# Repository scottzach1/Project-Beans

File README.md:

# Group 3 - Project beans

## Welcome to Project Beans.

Project Beans was a 2020 project by 6 VUW Engineering students to
deliver a model rocket for a client. An in-depth breakdown of the
projects scope, deliverables and current state can be obtained in-depth
within the documentation of this repository.

> Figure 1: Rocket Design Render

## Meet The Team

### Software

|  |  |  |
|:------------------------------------------------------------------------------------------------------------------------------------------------------|:---------------------------------------------------------------------------------------------------------------|:--------------------------------------------------------------------------------------------------------------|
| [Zac Scott](https://github.com/scottzach1)                                                                                                            | [Ron Crisostomo](https://github.com/crisosron)                                                                 | [Finlay Sargisson](https://github.com/sarrgi)                                                                 |

### Hardware

|  |  |  |
|:-------------------------------------------------------------------------------------------------------------------------------------------------------------|:-----------------------------------------------------------------------------------------------------------------|:---------------------------------------------------------------------------------------------------------------------------------------------|
| [Niels Clayton](https://github.com/Niels-Clayton)                                                                                                            | [William Fowler](https://github.com/Will-Fowler)                                                                 | [Billy Rob](https://gitlab.ecs.vuw.ac.nz/robbbill)                                                                                           |

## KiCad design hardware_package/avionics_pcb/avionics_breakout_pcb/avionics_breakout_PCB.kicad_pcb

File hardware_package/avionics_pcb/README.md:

# Avionics PCB's

> Description of the different avionics PCB's and libraries

## KiCad

- All PCB's will be designed using the KiCad Cross Platform and Open Source Electronics Design Automation Suite. A selection of custom footprints and symbols used in the following projects can be found in the `kicad_lib/` directory.

- All PCB's within this directory will be subject to standard ERC and DRC rule checks, which will be performed and checked by the CI pipeline.

## PCB's

| File             | Description       |
|:-----------------|:------------------|
| `avionics_base_station/`  | The avionics base station PCB will be used to connect the RFM98 LoRa radio to the [ESP8266 microcontroller](https://www.espressif.com/en/products/socs/esp8266), maintaining a small form-factor. This board is designed to be the final base station product. |
| `avionics_breakout_PCB/`  | The avionics breakout PCB will is the second prototype of the rocket hardware. This PCB will take all of the testing breakout boards that can be found [here](../bill_of_materials/bill_of_materials.md) in the BOM, and will integrate all of then onto a single compact board that is limited to a single side. This board will be used for extensive testing of the hardware in unison. |
| `Final_PCB/` | The avionics final PCB is the final iteration of the PCB. This board will take all of the individual components found on each of the breakouts, and will place them onto a single PCB. This board will also include power supplies for all components, including the ignition circuitry and servo motors.  |

## Libraries

| File             | Description       |
|:-----------------|:------------------|
| `kicad_lib/` | This directory contains a selection of custom footprints and symbols that have been used in the PCB's. This library currently contains footprints for the following parts:

- Adafruit Feather STM32F4D5 Breakout
- ESP8266 Node MCU microcontroller breakout
- Adafruit MPL3115A2 Barometer Breakout
- Adafruit MPU 6050 Breakout
- RFM98 LoRa Radio

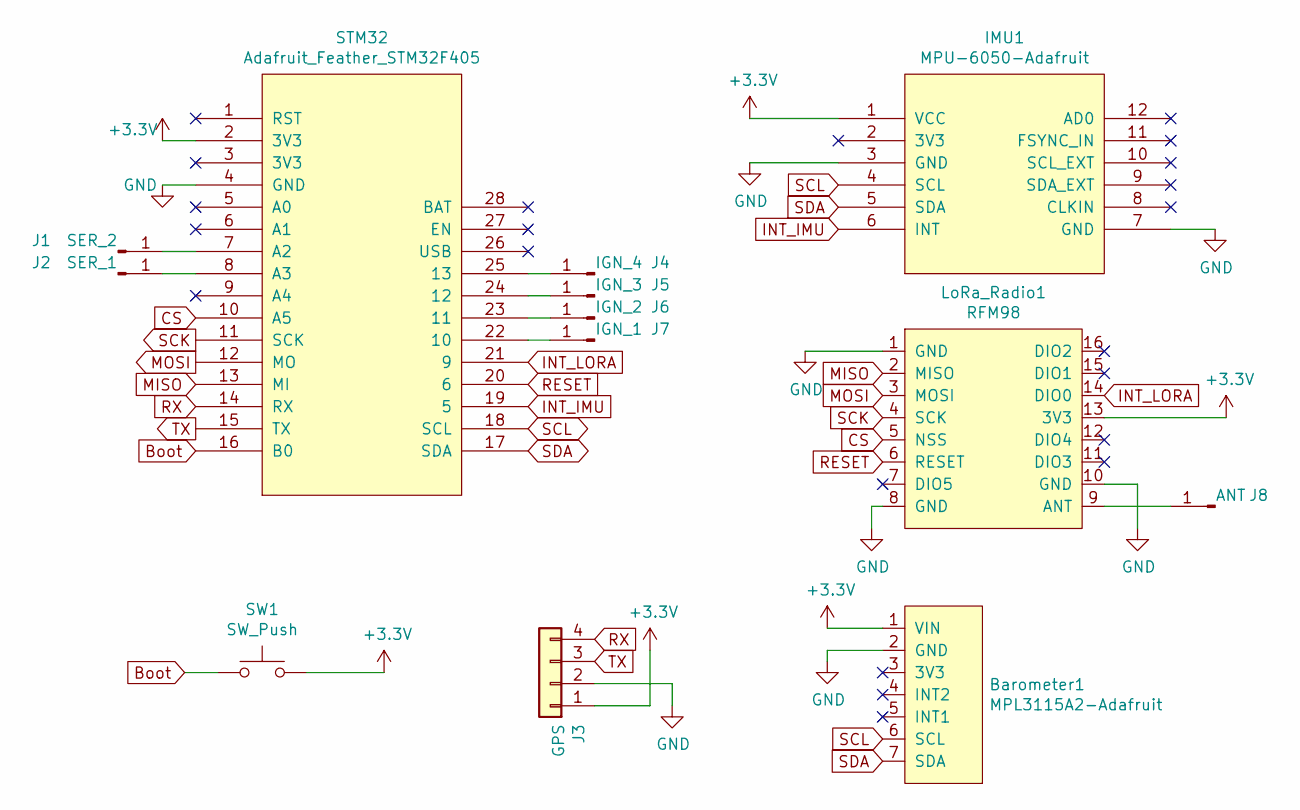
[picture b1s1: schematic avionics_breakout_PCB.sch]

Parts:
Barometer1: MPL3115A2-Adafruit
IMU1: MPU-6050-Adafruit; MPU6050-adafruit
J1: SER_2; SolderWire-0.1sqmm_1x01_D0.4mm_OD1mm
J2: SER_1; SolderWire-0.1sqmm_1x01_D0.4mm_OD1mm
J3: GPS; PinHeader_1x04_P2.54mm_Vertical
J4: IGN_4; SolderWire-0.1sqmm_1x01_D0.4mm_OD1mm
J5: IGN_3; SolderWire-0.1sqmm_1x01_D0.4mm_OD1mm
J6: IGN_2; SolderWire-0.1sqmm_1x01_D0.4mm_OD1mm
J7: IGN_1; SolderWire-0.1sqmm_1x01_D0.4mm_OD1mm
J8: ANT; SolderWire-0.1sqmm_1x01_D0.4mm_OD1mm
LoRa_Radio1: RFM98
STM32: Adafruit_Feather_STM32F405
SW1: SW_Push; SW_PUSH_6mm

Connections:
+3V3: Barometer1.1 (VIN), IMU1.1 (VCC), J3.1, LoRa_Radio1.13 (3V3), STM32.2 (3V3), SW1.2
Boot: STM32.16 (B0), SW1.1
CS: LoRa_Radio1.5 (NSS), STM32.10 (A5)
GND: Barometer1.2 (GND), IMU1.3 (GND), IMU1.7 (GND), J3.2, LoRa_Radio1.1 (GND), LoRa_Radio1.8 (GND), LoRa_Radio1.10 (GND), STM32.4 (GND)
INT_IMU: IMU1.6 (INT), STM32.19 (5)
INT_LORA: LoRa_Radio1.14 (DIO0), STM32.21 (9)
MISO: LoRa_Radio1.2 (MISO), STM32.13 (MI)
MOSI: LoRa_Radio1.3 (MOSI), STM32.12 (MO)
unnamed: J1.1, STM32.7 (A2)
unnamed: J2.1, STM32.8 (A3)
unnamed: J4.1, STM32.25 (13)
unnamed: J5.1, STM32.24 (12)
unnamed: J6.1, STM32.23 (11)
unnamed: J7.1, STM32.22 (10)
unnamed: J8.1, LoRa_Radio1.9 (ANT)
RESET: LoRa_Radio1.6 (RESET), STM32.20 (6)
RX: J3.4, STM32.14 (RX)
SCK: LoRa_Radio1.4 (SCK), STM32.11 (SCK)
SCL: Barometer1.6 (SCL), IMU1.4 (SCL), STM32.18 (SCL)
SDA: Barometer1.7 (SDA), IMU1.5 (SDA), STM32.17 (SDA)
TX: J3.3, STM32.15 (TX)

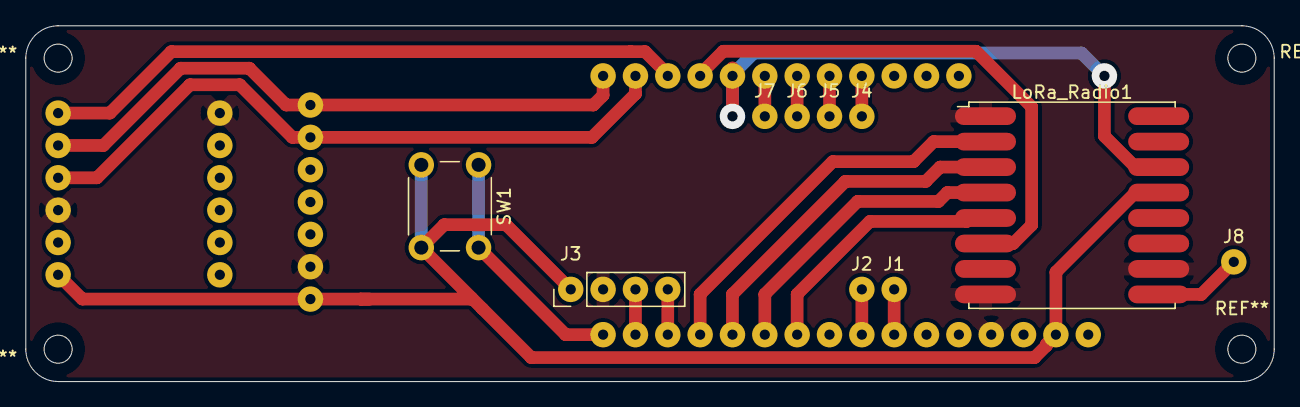
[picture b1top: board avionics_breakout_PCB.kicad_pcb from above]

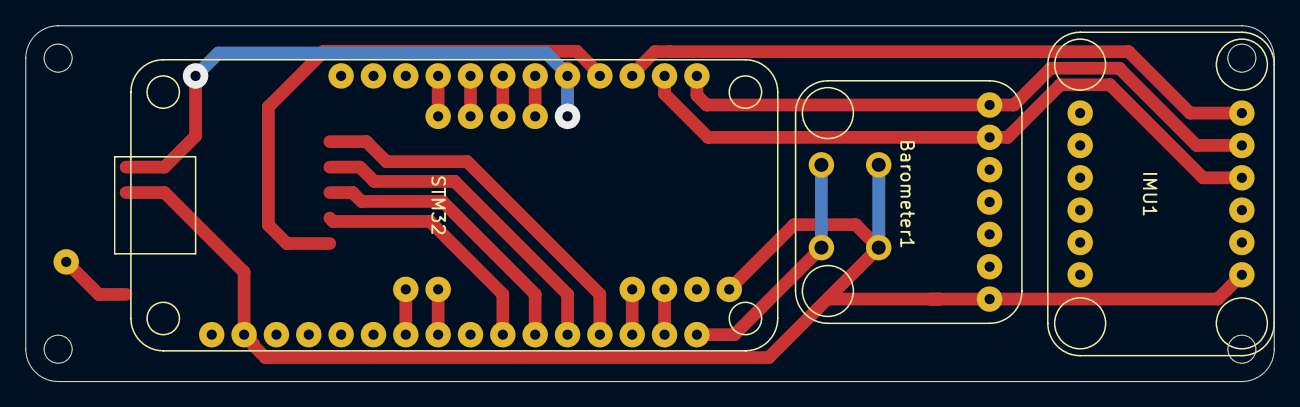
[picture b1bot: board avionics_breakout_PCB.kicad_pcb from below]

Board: 2 copper layers, 98.0 x 27.9 mm, 13 parts (3 on the bottom side), 21 nets.

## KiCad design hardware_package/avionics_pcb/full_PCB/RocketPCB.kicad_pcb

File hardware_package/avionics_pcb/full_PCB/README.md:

## Full PCB - Prototype 1 - Documentation

This PCB is designed to accomodate the STM32F405 processor, the accompanying sensors and peripherals, power circuitry and supporting passive and active electronic components required by the avionics package.

### Schematic
For the schematic we wanted to integrate as many components into the avionics package board as possible to reduce the size and cost associated with manufacutring. In this case the only sensors that are not integrated into the board are the MPU-6050, the GPS and the LoRa radio tranceiver which are on breakout boards connected by headers.

#### Power circuitry
The avionics package is designed to be powered off of a 2-cell LiPo battery supplying a nominal voltage of 7.4V. This is connected to the avionics board via a 3 pin JST connector. Included in series with the +7.4V pin is a fet and polyfuse to protect against reverse polarity and over current. The 7.4V is then passed to two regulator, a 3.3V linear regulator capable of supply up to 1A for the microprocessor and periphals and a 6V switching regulator capable of supplying up to 2A to both of the servos. So there is a +3.3V and a +6V rail. The ground is referenced to the negative terminal of the battery.

Regarding the 3.3V regulator, a fet and diode are included at the input so that when the battery is connected the 5V supplied by the voltage bus of the USB-C port is cut off by the fet. If the battery is not connected then the device can be powered off of the USB-C port. For verification and debug purporses, LEDs and test points were included at the output of both regulators and an additional test point included for ground. Lastly decoupling capacitors were included between the power rails and power inputs of each of the ICs to isolate any potential noise sources from interfering with the rest of the system.

#### STM32F405 and Adafruit feather design
The STM32F405 was chosen as our design is based on the Adafruit STM32F405 Feather Express development board [available here](https://learn.adafruit.com/adafruit-stm32f405-feather-express/downloads). From this development board we kept the microSD port, the USB-C connector, flash memory, and a redesigned 3.3V regulator. Components and features that we did not integrated from the Adafruit Feather included the USB battery charger and NeoPixel programmable LED. The battery charger was not included as this functionality would make the avionics package bulkier and it is not practical to charge a 2-cell LiPo using USB.

Both of the external oscillator crystals included in the Adafruit feather were not included in the design as the STM32F405 already contains a high speed internal RC oscillator which runs at 16MHz.

#### Sensors and peripherals
For the sensors and periphals, included in the schematic are the IMU, Lora radio tranceiver, barometer and GPS. All of these aside from the barometer are integrated into the PCB. The IMU, radio and gps have pads to connect the breakoutboards for these components via headers. The GPS, barometer and IMU all communicate via I2C protocol while the flash memory and radio module communicate via SPI protocol.

All the sensors and breakout boards are based off of Adafruit designs listed below:
[GPS](https://learn.adafruit.com/adafruit-mini-gps-pa1010d-module)
[Radio Tranceiver](https://learn.adafruit.com/adafruit-rfm69hcw-and-rfm96-rfm95-rfm98-lora-packet-padio-breakouts/downloads)
[IMU](https://learn.adafruit.com/mpu6050-6-dof-accelerometer-and-gyro?view=all)
[Barometer](https://learn.adafruit.com/using-mpl3115a2-with-circuitpython)

### PCB design
The PCB design uses 4 layers, the top and bottom are for signals, the 2nd layer is a ground plane and the 3rd layer is a +3.3V plane. The PCB can be sectioned into the power supply, breakout board pads, microprocessor, microSD card port, flash memory and barometer, all including their respective supporting components. Most of the anlogue circuity was segrated from the digital components to minimize EMI.

In terms of footprints, aside form the breakoutboard pads, pads for the futaba JR connectors, the poly fuse and flash memory, all the other footprints are surface mounted. This is to ensure the package remains small and compact.

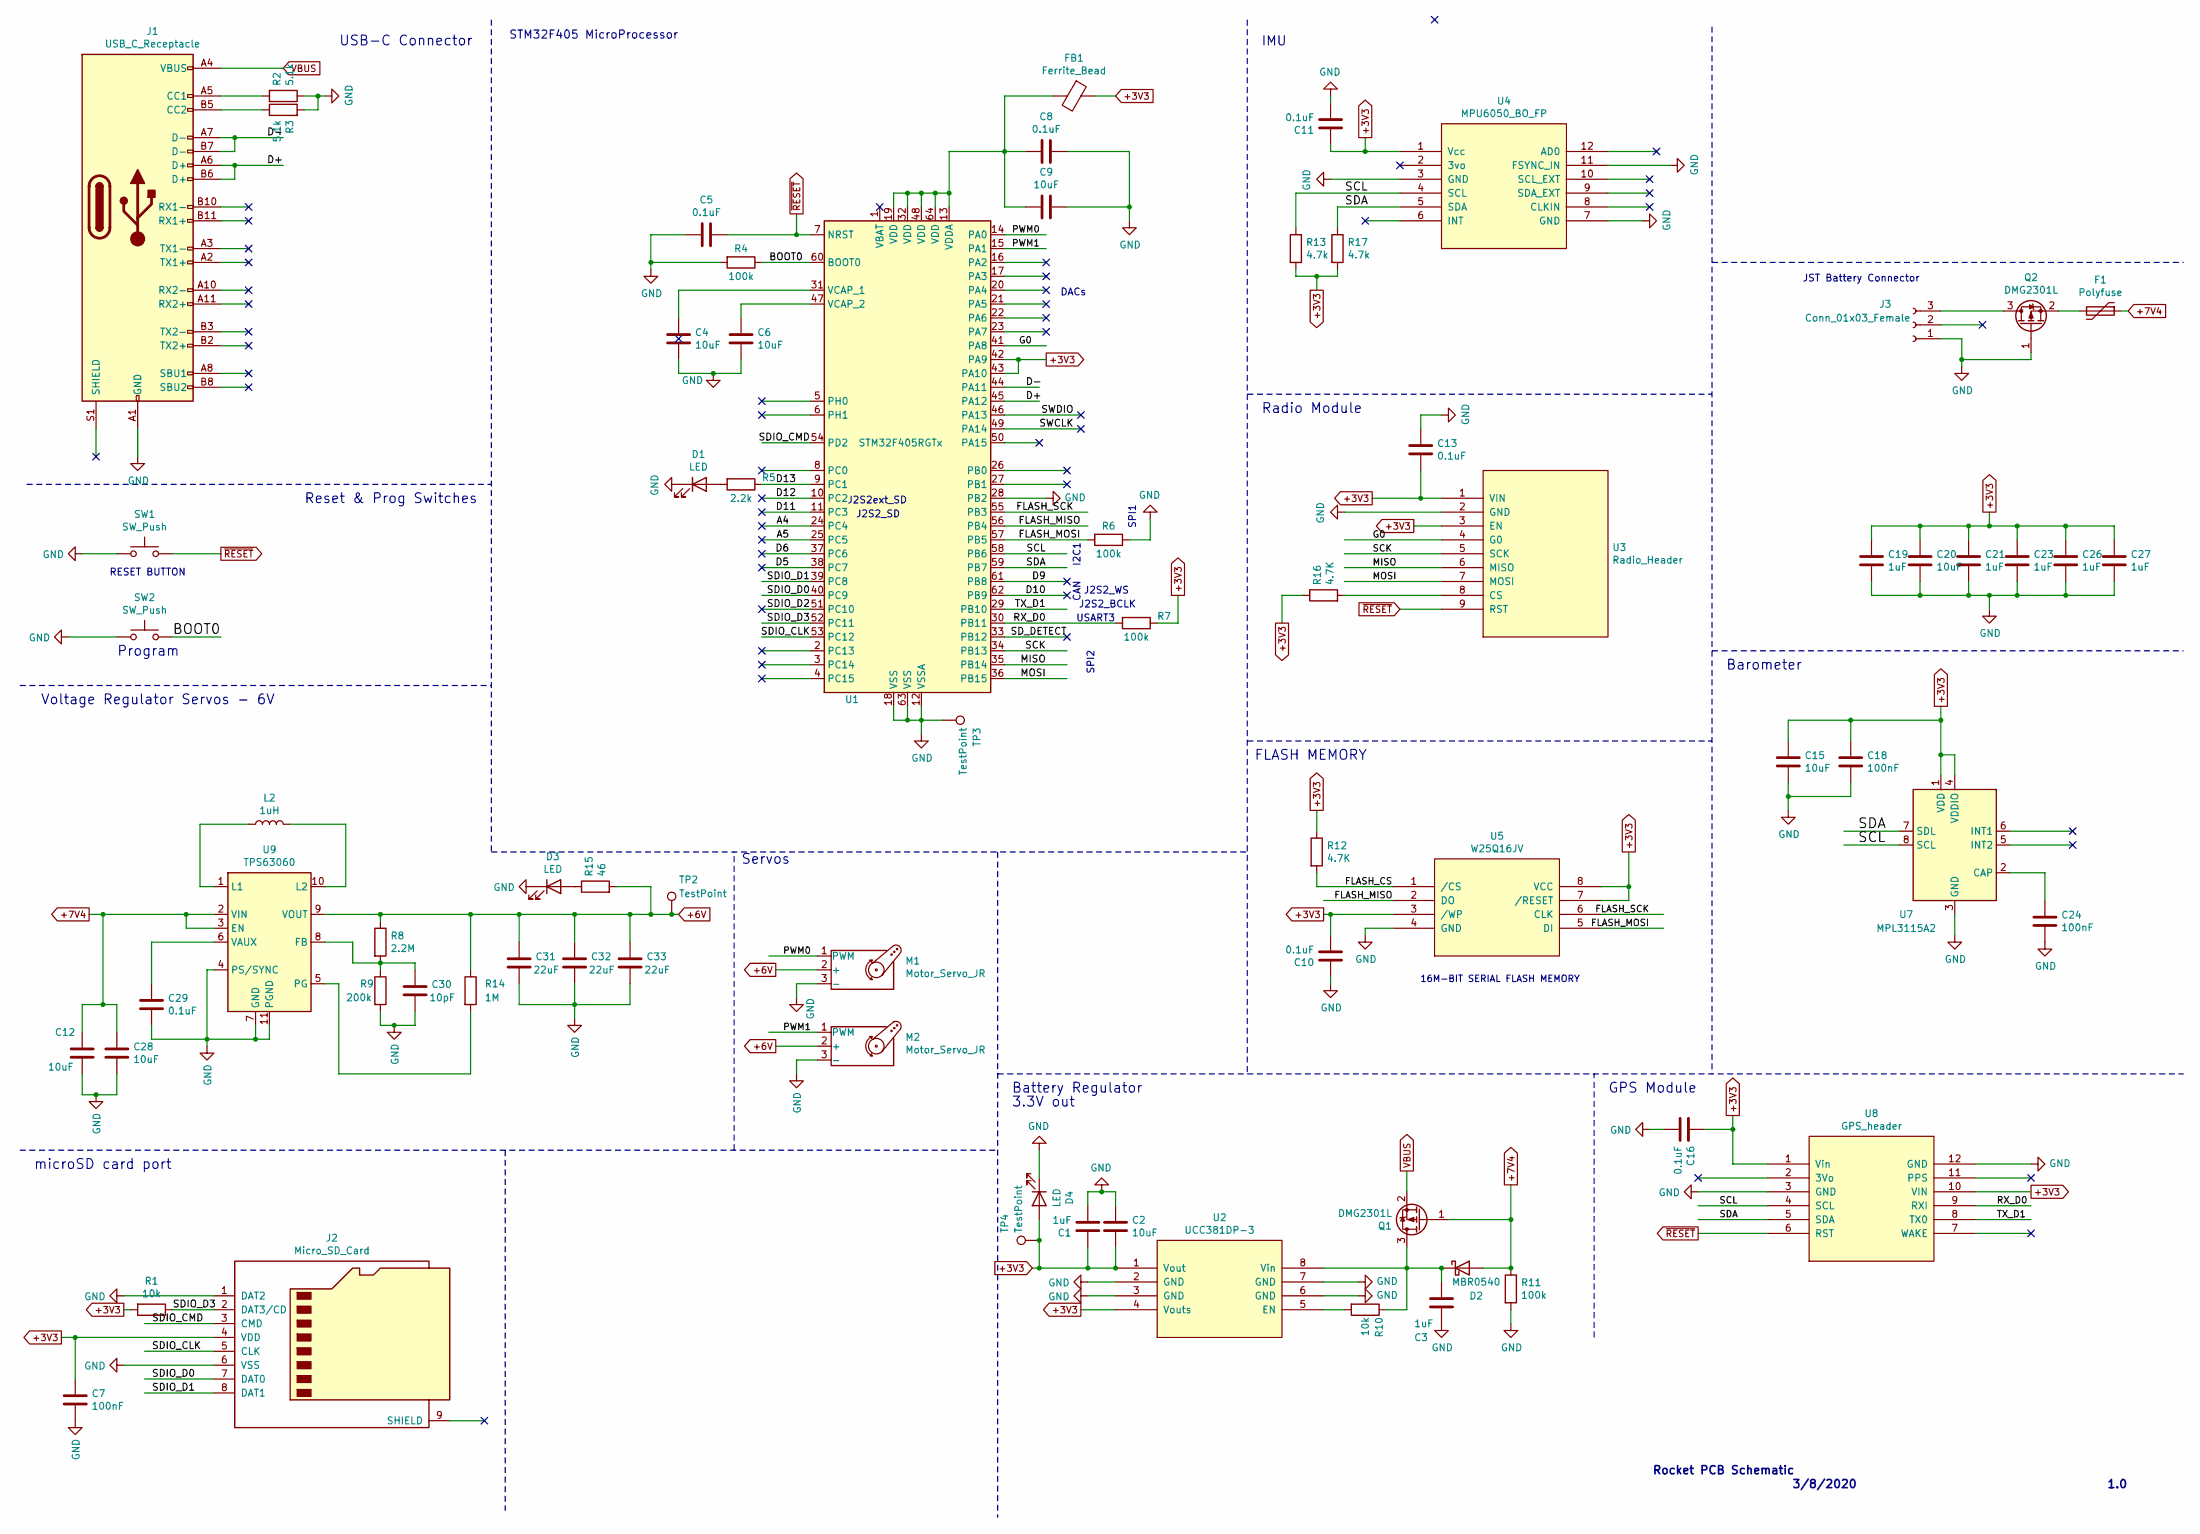
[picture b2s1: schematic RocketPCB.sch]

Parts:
C1, C3, C19, C21, C23, C26, C27: 1uF; C_0603_1608Metric
C2, C4, C6, C9, C12, C15, C20, C28: 10uF; C_0805_2012Metric
C5, C8, C10, C11, C13, C16, C29: 0.1uF; C_0603_1608Metric
C7, C18, C24: 100nF; C_0603_1608Metric
C30: 10pF; C_0603_1608Metric
C31, C32, C33: 22uF; C_0805_2012Metric
D1, D3, D4: LED; LED_0603_1608Metric_Pad1.05x0.95mm_HandSolder
D2: MBR0540; D_SOD-123
F1: Polyfuse; Fuse_Littelfuse_395Series
FB1: Ferrite_Bead; R_0402_1005Metric
J1: USB_C_Receptacle; USB_C_Receptacle_Palconn_UTC16-G
J2: Micro_SD_Card; microSD_HC_Hirose_DM3BT-DSF-PEJS
J3: Conn_01x03_Female; JST_XH_B3B-XH-A_1x03_P2.50mm_Vertical
L2: 1uH; L_0805_2012Metric
M1, M2: Motor_Servo_JR; JR_servo_connector
Q1, Q2: DMG2301L; SOT-23
R1, R10: 10k; R_0603_1608Metric
R2, R3: 5.1k; R_0603_1608Metric
R4, R6, R7, R11: 100k; R_0603_1608Metric
R5: 2.2k; R_0603_1608Metric
R8: 2.2M; R_0603_1608Metric
R9: 200k; R_0603_1608Metric
R12, R16: 4.7K; R_0603_1608Metric
R13, R17: 4.7k; R_0603_1608Metric
R14: 1M; R_0603_1608Metric
R15: 46; R_0603_1608Metric
SW1, SW2: SW_Push; SW_Push_SPST_NO_Alps_SKRK
TP2, TP3, TP4: TestPoint; TestPoint_Pad_D1.0mm
U1: STM32F405RGTx; LQFP-64_10x10mm_P0.5mm
U2: UCC381DP-3; SOIC127P599X175-8N
U3: Radio_Header; gps_header_footprint
U4: MPU6050_BO_FP; MPU6050-footprint
U5: W25Q16JV; W25Q16JV_footprint
U7: MPL3115A2; NXP_LGA-8_3x5mm_P1.25mm_H1.1mm
U8: GPS_header; GPS_header_fp
U9: TPS63060; Texas_S-PWSON-N10_ThermalVias

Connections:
+3V3: C1.1, C2.2, C7.1, C10.2, C11.1, C13.2, C15.1, C16.1, C18.1, C19.1, C20.1, C21.1, C23.1, C26.1, C27.1, D4.2 (A), FB1.1, J2.4 (VDD), R1.2, R7.1, R12.1, R13.2, R16.1, R17.2, TP4.1, U1.42 (PA9), U1.43 (PA10), U2.1 (Vout), U2.4 (Vouts), U3.1 (VIN), U3.3 (EN), U4.1 (Vcc), U5.3 (/WP), U5.7 (/RESET), U5.8 (VCC), U7.1 (VDD), U7.4 (VDDIO), U8.1 (Vin), U8.10 (VIN)
+6V: C31.1, C32.1, C33.1, M1.2 (+), M2.2 (+), R8.1, R14.1, R15.2, TP2.1, U9.9 (VOUT)
+7V4: C12.1, C28.1, D2.2 (A), F1.1, Q1.1 (G), R11.1, U9.2 (VIN), U9.3 (EN)
/A4: U1.24 (PC4)
/A5: U1.25 (PC5)
/BOOT0: R4.1, SW2.2, U1.60 (BOOT0)
/D5: U1.38 (PC7)
/D6: U1.37 (PC6)
/D9: U1.61 (PB8)
/D10: U1.62 (PB9)
/D11: U1.11 (PC3)
/D12: U1.10 (PC2)
/D13: R5.1, U1.9 (PC1)
/D+: J1.A6 (D+), J1.B6 (D+), U1.45 (PA12)
/D-: J1.A7 (D-), J1.B7 (D-), U1.44 (PA11)
/FLASH_CS: R12.2, U5.1 (/CS)
/FLASH_MISO: U1.56 (PB4), U5.2 (DO)
/FLASH_MOSI: R6.2, U1.57 (PB5), U5.5 (DI)
/FLASH_SCK: U1.55 (PB3), U5.6 (CLK)
/G0: U1.41 (PA8), U3.4 (G0)
/MISO: U1.35 (PB14), U3.6 (MISO)
/MOSI: U1.36 (PB15), U3.7 (MOSI)
/PWM0: M1.1 (PWM), U1.14 (PA0)
/PWM1: M2.1 (PWM), U1.15 (PA1)
/RX_D0: R7.2, U1.30 (PB11), U8.9 (RXI)
/SCK: U1.34 (PB13), U3.5 (SCK)
/SCL: R13.1, U1.58 (PB6), U4.4 (SCL), U7.8 (SCL), U8.4 (SCL)
/SDA: R17.1, U1.59 (PB7), U4.5 (SDA), U7.7 (SDL), U8.5 (SDA)
/SDIO_CLK: J2.5 (CLK), U1.53 (PC12)
/SDIO_CMD: J2.3 (CMD), U1.54 (PD2)
/SDIO_D0: J2.7 (DAT0), U1.40 (PC9)
/SDIO_D1: J2.8 (DAT1), U1.39 (PC8)
/SDIO_D2: U1.51 (PC10)
/SDIO_D3: J2.2 (DAT3/CD), R1.1, U1.52 (PC11)
/SD_DETECT: U1.33 (PB12)
/SWCLK: U1.49 (PA14)
/SWDIO: U1.46 (PA13)
/TX_D1: U1.29 (PB10), U8.8 (TX0)
GND: C1.2, C2.1, C3.2, C4.2, C5.1, C6.2, C7.2, C8.2, C9.2, C10.1, C11.2, C12.2, C13.1, C15.2, C16.2, C18.2, C19.2, C20.2, C21.2, C23.2, C24.2, C26.2, C27.2, C28.2, C29.2, C30.2, C31.2, C32.2, C33.2, D1.1 (K), D3.1 (K), D4.1 (K), J1.A1 (GND), J1.A12 (GND), J1.B1 (GND), J1.B12 (GND), J2.1 (DAT2), J2.6 (VSS), J3.1, M1.3 (-), M2.3 (-), Q2.1 (G), R2.1, R3.2, R4.2, R6.1, R9.2, R11.2, SW1.1, SW2.1, TP3.1, U1.12 (VSSA), U1.18 (VSS), U1.28 (PB2), U1.63 (VSS), U2.2 (GND), U2.3 (GND), U2.6 (GND), U2.7 (GND), U3.2 (GND), U4.3 (GND), U4.7 (GND), U4.11 (FSYNC_IN), U5.4 (GND), U7.3 (GND), U8.3 (GND), U8.12 (GND), U9.4 (PS/SYNC), U9.7 (GND), U9.11 (PGND)
unnamed: C3.1, D2.1 (K), Q1.3 (D), R10.1, U2.8 (Vin)
unnamed: C4.1, U1.31 (VCAP_1)
unnamed: C6.1, U1.47 (VCAP_2)
unnamed: C8.1, C9.1, FB1.2, U1.13 (VDDA), U1.19 (VDD), U1.32 (VDD), U1.48 (VDD), U1.64 (VDD)
unnamed: C24.1, U7.2 (CAP)
unnamed: C29.1, U9.6 (VAUX)
unnamed: C30.1, R8.2, R9.1, U9.8 (FB)
unnamed: D1.2 (A), R5.2
unnamed: D3.2 (A), R15.1
unnamed: F1.2, Q2.2 (S)
unnamed: J1.A5 (CC1), R2.2
unnamed: J1.B5 (CC2), R3.1
unnamed: J3.3, Q2.3 (D)
unnamed: L2.1, U9.1 (L1)
unnamed: L2.2, U9.10 (L2)
unnamed: R10.2, U2.5 (EN)
unnamed: R14.2, U9.5 (PG)
unnamed: R16.2, U3.8 (CS)
VBUS: J1.A4 (VBUS), J1.A9 (VBUS), J1.B4 (VBUS), J1.B9 (VBUS), Q1.2 (S)
~RESET~: C5.2, SW1.2, U1.7 (NRST), U3.9 (RST), U8.6 (RST)

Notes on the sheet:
DACs
RESET BUTTON
JST Battery Connector
USB-C Connector
Rocket PCB Schematic
3/8/2020
1.0
IMU
SPI2
USART3
J2S2_BCLK
J2S2_WS
CAN
SPI1
STM32F405 MicroProcessor
J2S2_SD
J2S2ext_SD
I2C1
microSD card port
Barometer
Program
Reset & Prog Switches
Battery Regulator
GPS Module
Radio Module
3.3V out
FLASH MEMORY
16M-BIT SERIAL FLASH MEMORY
Voltage Regulator Servos - 6V
Servos

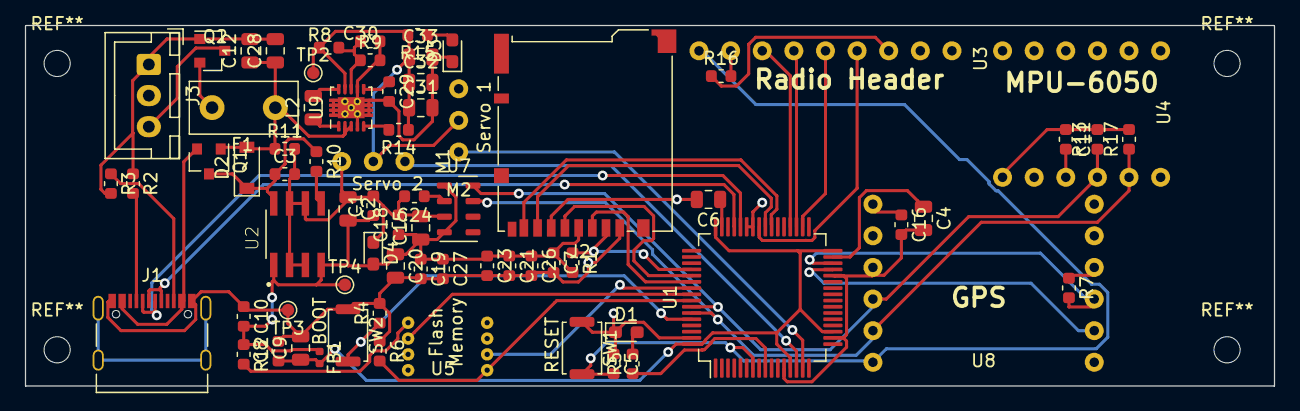
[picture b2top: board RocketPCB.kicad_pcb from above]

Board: 4 copper layers, 100.3 x 29.0 mm, 72 parts (0 on the bottom side), 47 nets.

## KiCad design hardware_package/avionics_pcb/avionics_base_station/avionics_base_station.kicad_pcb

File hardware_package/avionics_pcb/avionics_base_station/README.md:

# Avionics Base Station PCB

This PCB is designed to interface the NodeMCU microcontroller with the RFM98 radio module. This board will act as the base station that will connect the ground control computer.

This PCB has been designed for a single layer, meaning that it is feasible to mill this PCB.

To assemble this unit, either directly solder the NodeMCU unit to the board, or solder on female headers with which to connect it. Then solder on the RFM98 castellated module and connect a solid core wire to the antenna.

## Schematic

## PCB Routing

## Assembled Unit

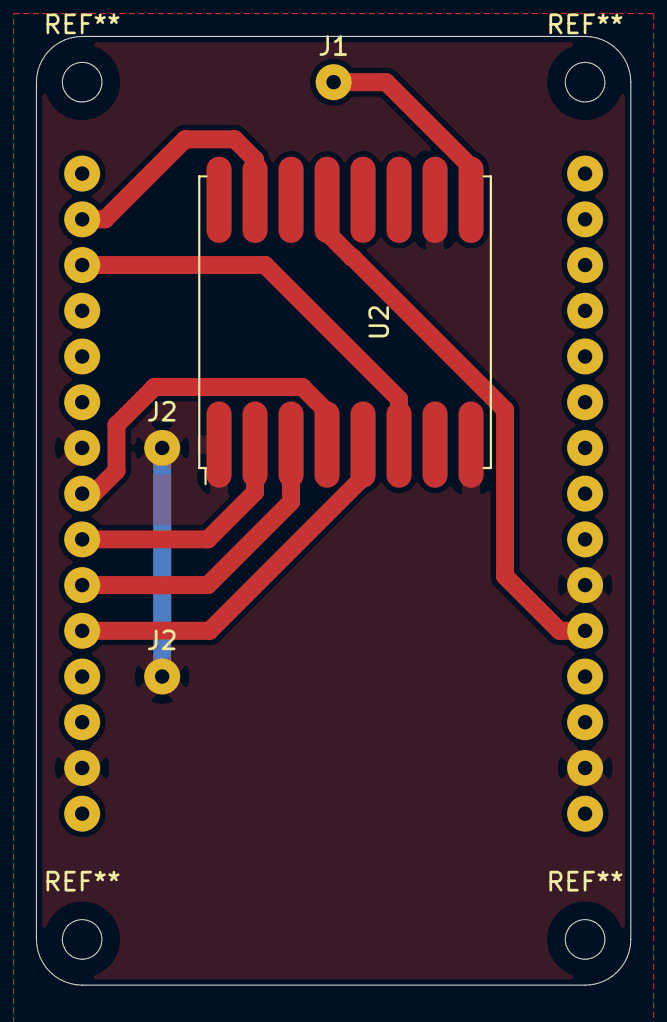
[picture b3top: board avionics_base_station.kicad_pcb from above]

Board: 2 copper layers, 33.0 x 52.7 mm, 5 parts (1 on the bottom side), 9 nets.

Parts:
J1: ANT; SolderWire-0.1sqmm_1x01_D0.4mm_OD1mm
J2, J2#2: GND_PASS; SolderWire-0.1sqmm_1x01_D0.4mm_OD1mm
U1: NODEMCU
U2: RFM98

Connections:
+3V3: U1.20, U2.13
GND: J2.1, J2#2.1, U1.2, U1.9, U1.17, U1.21, U2.1, U2.8, U2.10
unnamed: J1.1, U2.9
unnamed: U1.5, U2.5
unnamed: U1.6, U2.3
unnamed: U1.7, U2.2
unnamed: U1.8, U2.4
unnamed: U1.13, U2.6
unnamed: U1.14, U2.15

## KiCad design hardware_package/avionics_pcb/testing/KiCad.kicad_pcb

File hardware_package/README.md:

# Hardware Package

This directory is for all hardware related files, such as PCB designs,
CAD files etc...

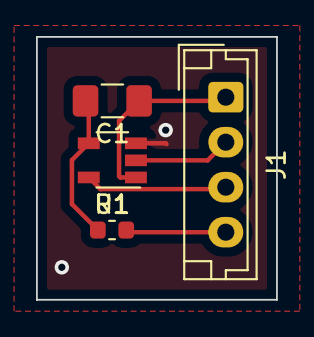
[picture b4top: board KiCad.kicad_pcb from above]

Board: 2 copper layers, 13.3 x 14.6 mm, 4 parts (0 on the bottom side), 5 nets.

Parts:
C1: C; C_1206_3216Metric_Pad1.42x1.75mm_HandSolder
J1: Conn_01x04; JST_EH_B4B-EH-A_1x04_P2.50mm_Vertical
R1: 100; R_0603_1608Metric
U1: AD8603; TSOT-23-5

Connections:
+5V: J1.3, U1.5
-5V: J1.2, U1.2
unnamed: C1.2, R1.1, U1.4
V_in: J1.4, R1.2
V_out: C1.1, J1.1, U1.1

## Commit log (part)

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2020-05-27 Began section 4.2 of architecture doc. Fixed file path typo in requirements doc in section 3.5
2020-05-28 Architecture Doc 4.4 Physical, start
2020-05-31 Started 4.2.2 - Added branching diagram and discussion around gitlab workflow
2020-06-03 Added break for UML component diagram image
2020-06-03 Architecture 4.4 including diagram & minor changes to 4.4.1
2020-06-04 Minor change to Error Propagation section 4.3.1
2020-06-04 Adds body paragraph for state diagrams part within section 4.1 logical
2020-06-05 Added sections 1-1.2 from project requirements
2020-06-06 Minor punctuation fixes
2020-06-07 Very minor changes to 4.1 of architecture document
2020-06-08 Set up bill of materials directory, added base files for items we will need to find.
2020-06-09 Edited content on linting and code conventions
2020-06-11 Began C++ conversion of existing sensors package
2020-06-11 draft of communication package
2020-06-12 Potential GPS options
2020-06-12 Adds Landing package.
    Adds `Lander.{cpp,h}` and `Parachute.{cpp,h}` to represent the Landing sub-package within the Landing package. In this commit, the Lander.c repersents the entire Landing package (handling all events 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
2020-06-12 Additional info for GPS options
2020-06-12 created all cpp and h classes. written basic pseudocode for headers.
2020-06-15 Added an extra option to the serial receiver document, This is a seed studio receiver that has available libraries and can be made into a breakout board for testing.
2020-06-15 Added 433MHz version of Grove LoRa radio
2020-06-16 Added more info to Linting subheading
2020-06-16 Started mock operations for sensors package
2020-06-17 minor touch ups
2020-06-18 Fixed .gitlab-ci.yml
2020-06-18 Reformated Communication Package so it all compiles.
2020-06-19 Formats Gimbal files to show valid C++ code for cpplint
2020-06-19 Added READMEs
2020-06-19 Added png version of powersupply diagram
2020-06-19 Readds changes previously made on the branch
2020-06-19 Buzzer transducer for rocket status indicator
2020-06-19 copied over 5.2 from architecture doc
2020-06-19 Status indicator prototype with diagrams
2020-06-19 Touchup previous commit adds missing delete lines
2020-06-19 refactored the hardware directory again, and changed input directory in the CI to match
2020-07-02 ordered parts
2020-07-22 removed unnecessary namespaces
2020-07-23 fixed test demo file style
2020-07-24 Refactors software package to comply with Platformio.
    In this commit, we add a working main cpp file that runs on the board (Credit to
    Niels on getting this working). We shuffle around the existing files to better comply
    with the recommended directory structures. We also add an entry the the .gitlab-ci.yml
    which should hopefully be on the right track (but I suspect that there will be issues
    with this). We also add an example test file that follows the recommended structure and
    includes files from the control library. This is a work in progress, and a lot of the
2020-07-28 Adds working library dependencies to .pio/libdeps
    In this commit, we add the library dependencies for the hardware into
    the project level library dependencies directory. This means hopefully
    platformio should be able to recognise the libraries on a fresh clone.
2020-07-29 Edits Start -> 1.3.1
2020-07-30 Added basic setup of Catch2 Testing Suite
    The Catch2 testing suite is a very simple C++ unit testing suite that
    requires the usage of a single header file `catch.hpp` in order to write
    unit tests. This is a temporary endeavour until the team finalizes what
    testing suite to use (PIO Unit Testing or something else). The usage of
    Catch2 in this case is for demo purposes of gcov/gcovr only.
2020-07-30 Adds brief comment for Linux.
2020-07-31 Added *.html to gitignore
    This is more of an experimental commit because im not sure what will
    happen to the job artifacts of the unit testing pipeline when the html
    files for code coverage reports are added to the gitignore.
2020-07-31 Added images of assembly
2020-07-31 Finished and edited Sec. 4.8
2020-08-04 Includes sample code from STM32SD library in main.cpp
    In this commit, we introduce example code from the stm32duino library
    into the main.cpp file. To make room for this, we refactor the existing
    dummy code for the MPU into its own respective method. The SD setup
    code is introduced into a `void setup_sd(void)` method. The sample
    code used within this commit can be seen at the following link:
    https://github.com/stm32duino/STM32SD/blob/master/examples/ReadWrite/ReadWrite.ino
2020-08-05 Creates Platformio subprojects
    In this commit we move the contents from the first
    project and move them into 2 different subprojects.
    We have a 'development' and 'testing' project. The
    development project is will contain all of the
    finalised code whereas the testing project will
    contain various methods to check whether the
2020-08-05 Updates to scripts, gitignore and added basic module
    The module added is to serve as a demo on how the tests and code
    coverage works with the scripts.
2020-08-05 Modified gitignore to include code coverage metadata. Added basic module for demo purposes
2020-08-05 Added servos with gear relationships to gimbal tube.
2020-08-05 Update more info to code_coverage README
2020-08-05 Updated log, added prototype 1 and 2 directories.
2020-08-05 Added tests for Logging package
2020-08-06 Added info on unit testing, PIO and code coverage in architecture doc
2020-08-06 Battery Charger
2020-08-06 Adds README.md to software_package/ explaining project structure.
    In this commit, we add a README.md in the `software_package/`
    directory outlining each of the platformio projects as well as
    an explanation of the PlatformIO project structure in general.
2020-08-06 Testing PlatformIO pipeline.
2020-08-07 Updated Project timeline
2020-08-07 Refactors master into new project structure.
    In this commit we refactor the codebase from master
    into the `development/` directory. This included
    moving the new test suites as well as slightly
    tweaking code coverage (Had a quick call with Ron).
2020-08-10 Reads data from the Barometer.
    The code now can read data from the Barometer. At the moment,
    sadly this is reading an altitude of 25k meters above Sea level.
    As we are breathing I suspect there might be something wrong with
    how things are setup at the moment.
2020-08-13 added method stubs for hardware libraries
2020-08-13 updated cpplint to exclusively target packages we are developing
2020-08-17 Reformat project_requirements directory to comply with linter settings.
2020-08-19 Updated unit-test job to actually execute unit tests
2020-08-21 Fixed readme
2020-08-27 Added a LoRa testing worspace and directory for the feather STM32, Added the radiolib library to the project, and tested some basic code to check that it was possible to upload to the feather
2020-08-27 Removed .pio directory from the gitignore. this will allow for locally installed libraries to be avalable on the reposetory
2020-08-30 The ESP is able to connect to the lora module and send and recieve packages, However the STM is currently unable to connect to the module, and will hang when initialized
2020-09-01 Update .gitlab-ci.yml to not execute unit tests in platformio job
2020-09-03 Pre-test methods setup
2020-09-03 Updated platformio environments
2020-09-06 Refactors IMU into new hardware libraries
    In this commit, we refactor the IMU code into the new
    libraries. We also fix a couple compiler warnings (would
    have lead to memory leak) within the SD logic and tidy
    up the main.cpp file. We also provide a simple example
    of how it should be used including initialisation and
    within loop().
2020-09-06 Refactors barometer into new library style.
    In this commit, we refactors the barometer into the new
    library format. We also provide an implementation of how
    it can be used within `main.cpp`.
2020-09-07 Tests the code on the rocket hardware.
    In this commit, we test the code on the hardware and
    fix any of the issues that we were encountering. One
    of the notable bugs that we had to fix was the Arduino
    `printf` function does not support `%f`. Unfortunately,
    due to issues with the SD card we are not able to verify
    whether it is working as intended. The barometer is also
2020-09-11 Several components have been created, the gimbal has been revised.
2020-09-14 Updated gimbal for attachment to rocket body.
2020-09-15 Setup of PCB for prototype 1, includes headers for breakout boards.
2020-09-15 Added IMU Headers
2020-09-16 Added outline for changes in 4.1 UML classes
2020-09-16 Updated 4.1 of architecture doc to include more info on states
2020-09-16 Introduces debug.h containing debugging wrapper for Serial print commands.
    In this commit, we create a wrapper for Serial.printf and Serial.println
    functions depending on a set debug level. This level can be set via the
    build arguments. However, if not set the default can be manually set
    within the header file.
2020-09-17 Refoctor the hardware directory to move the PCB design to a single location, created footprints and symbols for each of the boards we will be adding to the PCB
2020-09-17 updated log_lora() stub to log_radio() to keep with abstract convention
2020-09-17 Implemented state pattern
    This commit introduces some files to do with the state management of the
    rocket. Currently, there are 2 important concepts, The StateMachine
    class and the States class. The StateMachine construct serves the
    purpose of executing the actions that need to be undertaken in a
    specific state. State instances define a specific state the rocket can
    take, and the actions the rocket must perform while in that state.
2020-09-17 Updated the footprint library for the avionics board
2020-09-18 Large commit. updated gimbal, added Andres rocket, still need modify it.
2020-09-18 Finalised the breakout board PCB
2020-09-19 Fixed a refactoring issue with the testing directory
2020-09-20 Edit Wired interrupts to STM pins
2020-09-24 Began adding footprints, created new PCB layout
2020-09-25 Added experimental changes to code coverage
2020-09-26 Finished the new PCB layout for the breakout avionics PCB
2020-09-28 filled out IMU pre-launch tests
2020-09-28 Editied Circuit viewpoint and started on hardware
2020-09-29 Proper Commit
    Commits 636815e8776a929b040eceeee2fefa5baa9a2a9d was pushed under the
    assumption that changes to the .gitlab-ci.yml file were staged. They
    were not. whoops... This commit should have these changes staged
2020-09-30 Removed redundant directory and updated the gimbal progress log
2020-09-30 added link to readme
2020-09-30 Made a slight update to the BOM so that it fits the PCB readme. The BOM will however need a complete overhaul, splitting into two section. One section for the breakouts and prototyping, then another 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
2020-10-01 Updates to test template location, script and readme
    Turns out that PIO does some extra stuff on files placed directly in `/test` of a PIO project. This caused issues with the testing and code coverage generation. The test template has now been moved i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
2020-10-03 Assigned additional footprints adding headers for radio and GPS
2020-10-04 Draft of development readme
2020-10-04 Added hardrware description and table. Fixed top level link (hopefully)
2020-10-04 Attempt (2) at fixing link
2020-10-05 Implements mapping from upper to lower limits for servos.
    In this commit, Billy and I play with the servos and find the
    respective upper and lower limits for both of the servos. It is
    worth noting that the limits differ for each of the servos, in
    both offset and width. This means that we will need to keep
    track of both. Currently we are writing to this using the
    Arduino map function from 0 to 100 setting the value from a float
2020-10-06 Adds mpu_testing project to read quaternians from the mpu.
    In this commit, we add a demo library with the libraries
    installed that are required to read the Yaw Pitch and Rotation
    of the rocket.
2020-10-06 Removed additional oscillators.
2020-10-11 Fixed IMU, USB & JR conn fp/p/o conflict, laid out PCB blocks
2020-10-11 Linked in a diagram that was missing
2020-10-11 Continued routing pins, 18 left
2020-10-12 Finished routing and laying out first iteration of final PCB
2020-10-12 Added more to testing readme
2020-10-13 Proofread and added to requirements document
2020-10-14 Added contributions
2020-10-14 Added more info on assumptions and glossary for architecture doc
2020-10-16 Completed Full PCB documentation
2020-10-16 Completed the LoRa base station PCB documentation
2020-10-16 Fixes conflicts regarding sd_card testing.
2020-10-21 Removes personas, project charter, and stakeholder register for handover.
